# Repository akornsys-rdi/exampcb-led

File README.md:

exampcb-led
===========

Simple example pcb

## Intention ##
Board designed to serve as a simple example of design in CAD. It is also designed to be easy to solder, cheap and straightforward.

## Functioning ##
This analog circuit fade a LED off and on smoothly, using a single rail power (5V).

## ToDo ##
Changes to be implemented in the next version:
- Power over USB. miniUSB or microUSB?
- Footprint for capacitors to 200mil
- Replace the LED divisor by a resistive divider or zener.
- In silkscreen, change the text "YELLOW" by the text "LED"
- Increase the version number

## Derivative ##
This design is a revision of the original made for *OSHWCon 2011* by *Synusia* (kwendenarmo).

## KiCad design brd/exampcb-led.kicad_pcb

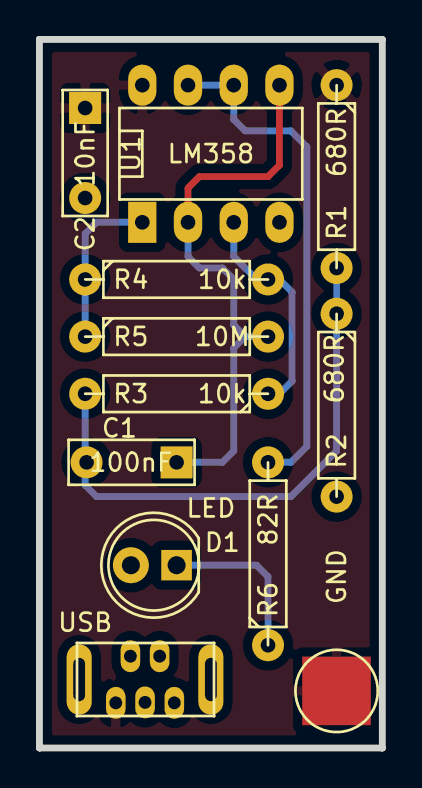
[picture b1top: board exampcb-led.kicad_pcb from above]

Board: 2 copper layers, 19.1 x 39.4 mm, 13 parts (0 on the bottom side), 8 nets.

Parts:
C1: 100nF; C_Rect_L7_W2.5_P5
C2: 10nF; C_Rect_L7_W2.5_P5
D1: LED; LED-5MM
J1: USB; UE25-BEx5-10x
J2: 5V; 1pin
J3: GND; 1pin
R1, R2: 680R; R4-LARGE_PADS
R3, R4: 10k; R4-LARGE_PADS
R5: 10M; R4-LARGE_PADS
R6: 82R; R4-LARGE_PADS
U1: LM358; DIP-8__300_ELL

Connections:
GND: C2.2, D1.2, J1.5, J3.1, R2.2, U1.4
unnamed: C1.1, R5.2, U1.2, U1.5
unnamed: C1.2, R1.2, R2.1, R3.2
unnamed: D1.1, R6.1
unnamed: R3.1, R4.2, U1.3
unnamed: R4.1, R5.1, U1.1
unnamed: R6.2, U1.6, U1.7
VCC: C2.1, J1.1, J2.1, R1.1, U1.8

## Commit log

2014-12-05 upload files
2015-11-10 new: dev: nuevo form-factor, cambio divisor y conector USB !wip
2020-04-02 añadido ToDo a README
2020-04-02 subidos gerbers

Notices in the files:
brd/exampcb-led.kicad_pcb:
Copyright (C) 2015 kwendenarmo
Released under GNU/GPL 3 License
https://www.gnu.org/licenses/gpl.html
